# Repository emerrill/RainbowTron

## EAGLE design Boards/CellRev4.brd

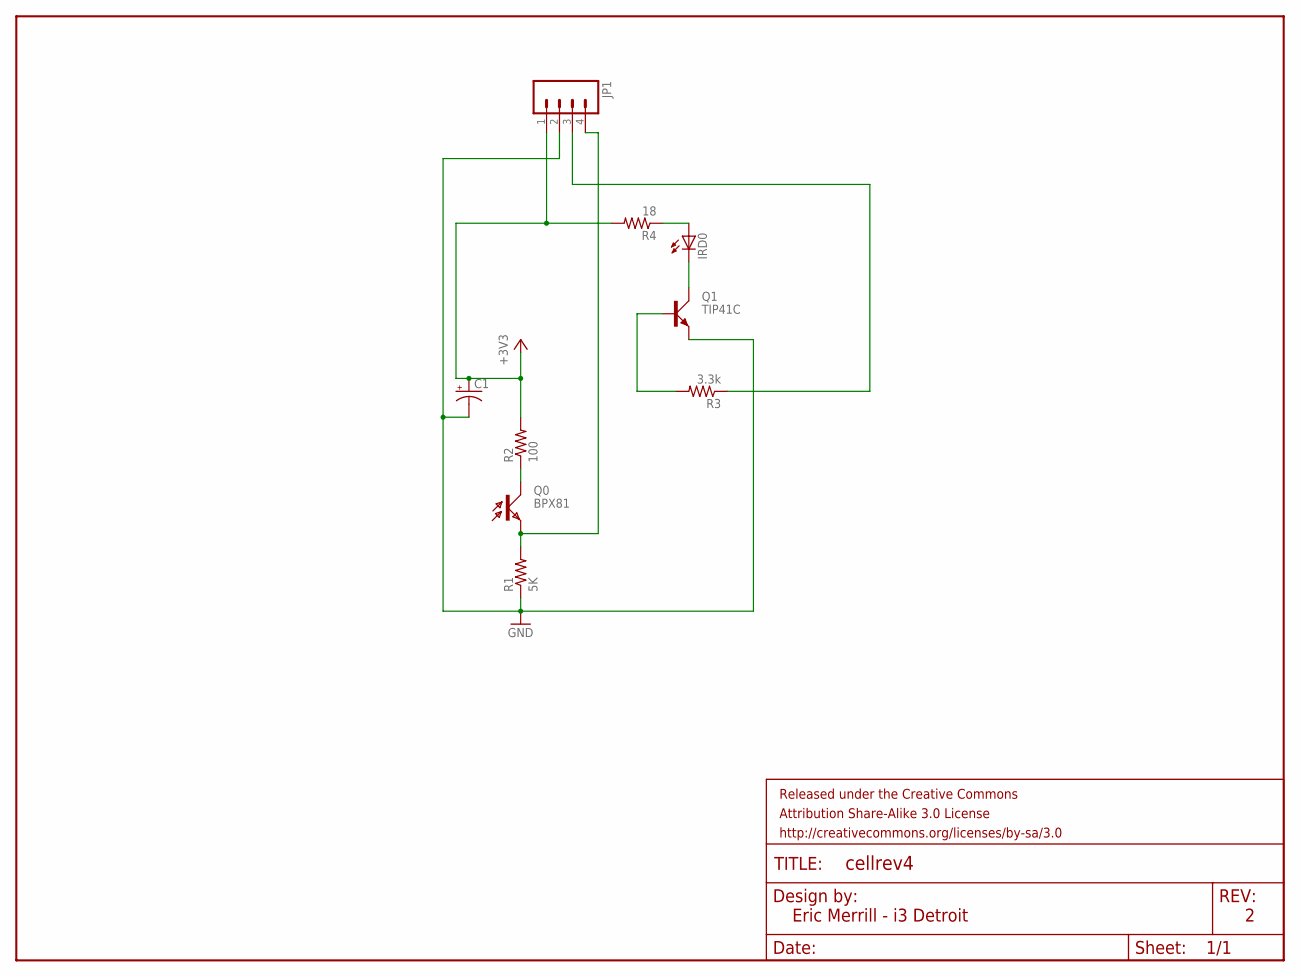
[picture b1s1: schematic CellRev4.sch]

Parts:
C1: CAP_POLPTH1; CPOL-RADIAL-100UF-25V
FRAME1: FRAME-LETTER; CREATIVE_COMMONS
IRD0: LED5MM
JP1: M04POLAR; MOLEX-1X4
Q0: BPX81
Q1: TIP41C; TO220AV
R1: 5K; 0207/10
R2: 100; 0207/10
R3: 3.3k; 0207/10
R4: 18; 0207/10

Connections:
+3V3: C1.1 (+), JP1.1, R2.2, R4.2
GND: C1.2 (-), JP1.2, Q1.E, R1.1
unnamed: Q0.C, R2.1
unnamed: Q1.B, R3.2
unnamed: IRD0.K (C), Q1.C
unnamed: IRD0.A, R4.1
SENSE: JP1.4, Q0.E, R1.2
SWITCH: JP1.3, R3.1

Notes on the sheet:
Eric Merrill - i3 Detroit

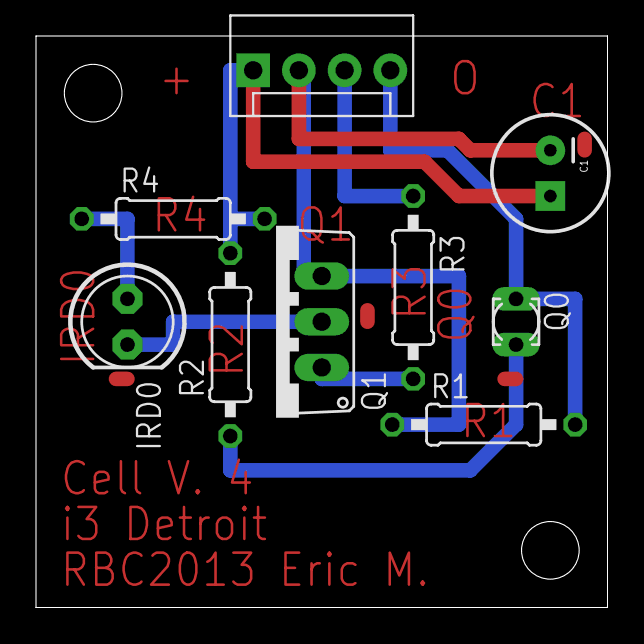
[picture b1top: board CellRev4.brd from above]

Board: 2 copper layers, 31.8 x 31.8 mm, 10 parts (0 on the bottom side), 8 nets.

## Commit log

2013-07-02 Adding the latest Rev of boards.
2014-05-08 Loading all the RainbowTron files from July 2013.

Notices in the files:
parts and their libraries:
SparkFun-Connectors: Licensing: CC v3.0 Share-Alike You are welcome to use this library for commercial purposes.
SparkFun-Aesthetics: Released under the Creative Commons Attribution Share-Alike 3.0 License
SparkFun-Aesthetics: http://creativecommons.org/licenses/by-sa/3.0
